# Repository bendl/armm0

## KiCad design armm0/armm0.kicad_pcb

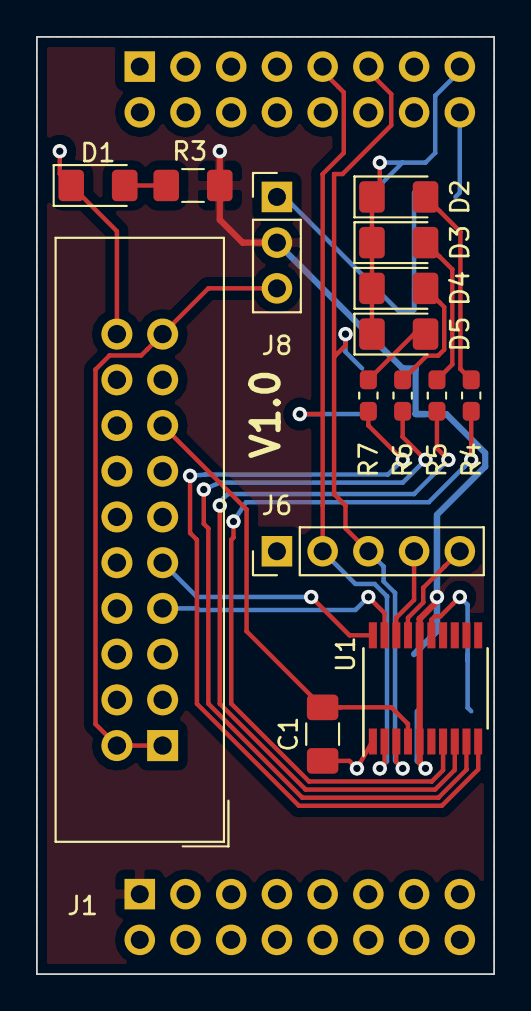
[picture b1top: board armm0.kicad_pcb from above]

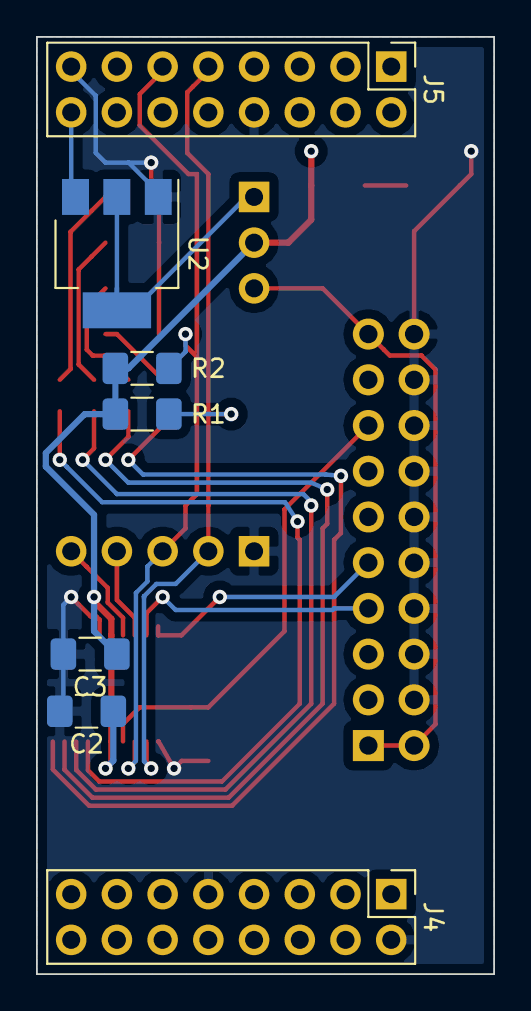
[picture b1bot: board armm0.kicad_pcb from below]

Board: 2 copper layers, 25.4 x 52.1 mm, 22 parts (7 on the bottom side), 21 nets.

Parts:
C1: 100nF; C_1206_3216Metric_Pad1.42x1.75mm_HandSolder
C2: 4.7uF; C_1206_3216Metric_Pad1.42x1.75mm_HandSolder
C3: 1uf; C_1206_3216Metric_Pad1.42x1.75mm_HandSolder
D1, D2, D3, D4, D5: LED; LED_1206_3216Metric_Pad1.42x1.75mm_HandSolder
J1: Conn_02x10_Odd_Even; IDC-Header_2x10_P2.54mm_Vertical
J4, J5: Conn_02x08_Odd_Even; PinHeader_2x08_P2.54mm_Vertical
J6: Conn_01x05_Male; PinHeader_1x05_P2.54mm_Vertical
J8: Conn_01x03_Male; PinHeader_1x03_P2.54mm_Vertical
R1, R2: 4.7k; R_1206_3216Metric_Pad1.42x1.75mm_HandSolder
R3: R; R_1206_3216Metric_Pad1.42x1.75mm_HandSolder
R4, R5, R6, R7: 50; R_0603_1608Metric_Pad1.05x0.95mm_HandSolder
U1: STM32F070F6Px; TSSOP-20_4.4x6.5mm_P0.65mm
U2: LD1117S33TR_SOT223; SOT-223-3_TabPin2

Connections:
+3V3: C2.1, C3.1, J4.1, J8.2, R1.1, R2.1, R3.1, U1.5, U1.16
+5V: J5.16, U2.3
BOARD_3V3: J8.1, U2.2
GND: C1.2, C2.2, C3.2, D1.1, D2.1, D3.1, D4.1, D5.1, J1.4, J1.6, J1.8, J1.10, J1.12, J1.14, J1.16, J1.18, J1.20, J4.2, J4.9, J5.8, J5.15, J6.1, U1.1, U1.15, U2.1
I2C1_SCL: J5.11, J6.3, R2.2, U1.3
I2C1_SDA: J5.9, J6.2, R1.2, U1.2
LED_DBUG1: R7.1, U1.10
LED_DBUG2: R6.1, U1.9
LED_DBUG3: R5.1, U1.8
LED_DBUG4: R4.1, U1.7
NRST: C1.1, J1.15, U1.4
unnamed: D1.2, R3.2
unnamed: D2.2, R4.2
unnamed: D3.2, R5.2
unnamed: D4.2, R6.2
unnamed: D5.2, R7.2
STLINK_3V3: J1.1, J1.2, J1.19, J8.3
SWCLK: J1.9, U1.20
SWDIO: J1.7, U1.19
USART1_RX: J6.4, U1.18
USART1_TX: J6.5, U1.17

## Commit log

2018-08-01 board: Init
2018-08-01 board: Everything is upside down
2018-08-02 armm0: Add eagle project
2018-08-04 sch: Add Conn_02x08 for shorter board
2018-08-04 sch: Add footprints for Conn_02x08
2018-08-04 sch: stlink: Update stlink pinout
2018-08-04 sch: Flip Conn_02x08 pin headers for upside down insertion to master board
2018-08-04 sch: Switch between board or stlink power source with 3pin selector
2018-08-04 pcb: Some wiring done
2018-08-04 pcb: Update
2018-08-05 sch: Use resistor array for debug leds
2018-08-05 pcb: All connected
2018-08-05 pcb: Fixed header distance
2018-08-05 pcb: Removed name
2018-08-05 sch: LED_DBUGn
2018-08-05 pcb: Connected LEDs and I2Cs
2018-08-07 pcb: Flip stlink connector to prevent clash with 5 pin header
2018-08-08 pcb: Resize to exactly 1x2 inches to save on costs
2018-08-08 gerb: Add gerbers
